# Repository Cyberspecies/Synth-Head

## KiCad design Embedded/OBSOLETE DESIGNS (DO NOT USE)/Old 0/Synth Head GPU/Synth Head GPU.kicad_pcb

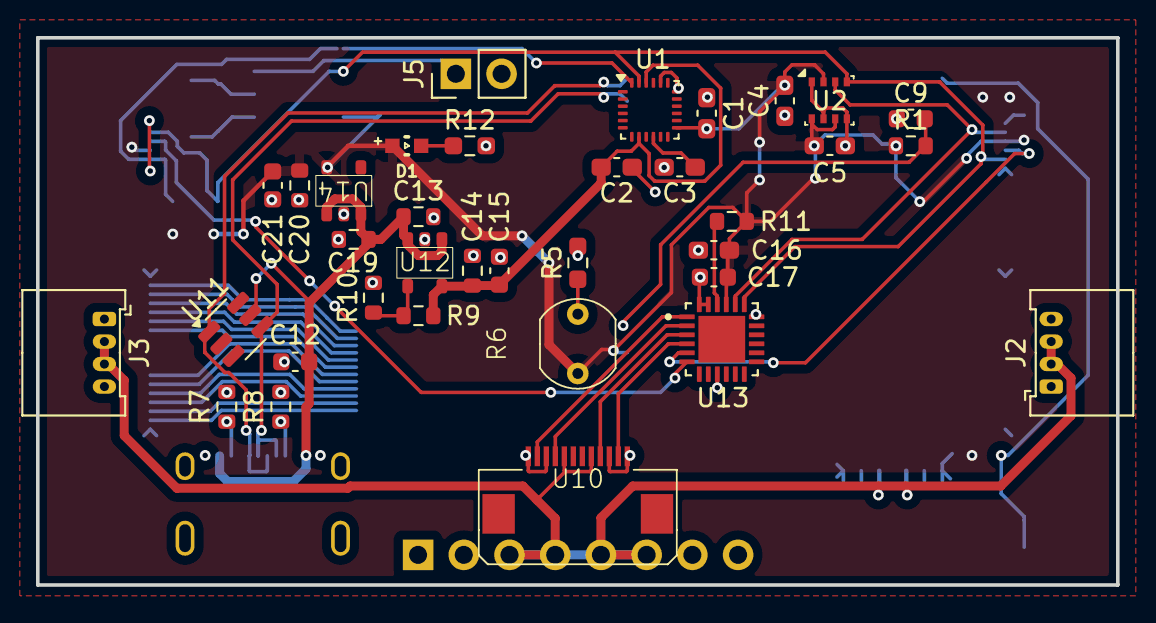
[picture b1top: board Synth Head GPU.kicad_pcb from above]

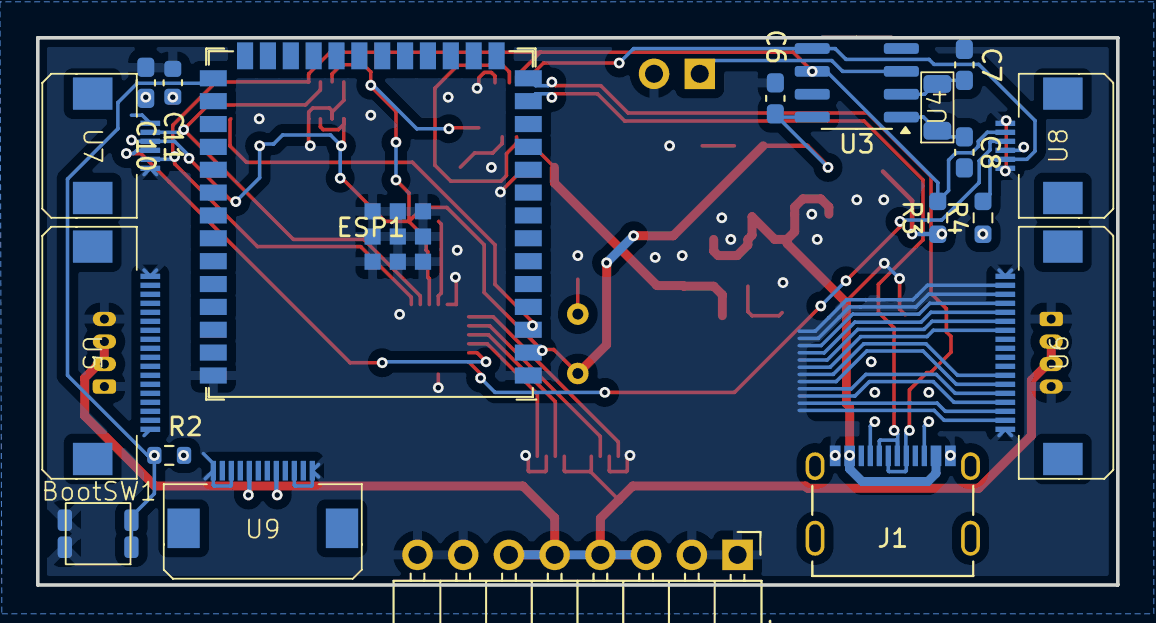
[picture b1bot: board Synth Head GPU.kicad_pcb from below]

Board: 2 copper layers, 60.0 x 30.4 mm, 54 parts (19 on the bottom side), 38 nets.

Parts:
BootSW1: SW_Push; Button-R-667843
C1, C2, C3, C6: 0.1uF; C_0603_1608Metric_Pad1.08x0.95mm_HandSolder
C4, C5: 100nF; C_0603_1608Metric_Pad1.08x0.95mm_HandSolder
C7, C8: 8pf; C_0603_1608Metric_Pad1.08x0.95mm_HandSolder
C9: 1uF; C_0603_1608Metric
C10, C16: 22uF; C_0603_1608Metric_Pad1.08x0.95mm_HandSolder
C11, C17: 0.1uF; C_0603_1608Metric
C12, C15, C21: 10uF; C_0603_1608Metric
C13, C14, C19, C20: 1uF; R_0603_1608Metric
D1: WL-SMCW_0603
ESP1: ESP32-S3-WROOM-1; ESP32-S3-WROOM-1U
J1: 10171746-00021LF; AMPHENOL_10171746-00021LF
J2, J3: JST [D]; Molex_PicoBlade_53048-0410_1x04_P1.25mm_Horizontal
J4: JST [G]; PinHeader_1x08_P2.54mm_Horizontal
J5: Coin Cell; PinHeader_1x02_P2.54mm_Vertical
R1, R2, R11: 10K; R_0603_1608Metric
R3, R4, R5: 10K; R_0603_1608Metric_Pad0.98x0.95mm_HandSolder
R6: R_Photo; Photoresistor Aliexpress
R7, R8: 5.1K; R_0603_1608Metric
R9: 75K; R_0603_1608Metric
R10: 60K; R_0603_1608Metric
R12: 65; R_0603_1608Metric_Pad0.98x0.95mm_HandSolder
U1: ICM-20948; InvenSense_QFN-24_3x3mm_P0.4mm
U2: BME280; Bosch_LGA-8_2.5x2.5mm_P0.65mm_ClockwisePinNumbering
U3: MCP7940N-xSN; SOIC-8_3.9x4.9mm_P1.27mm
U4: MP05346
U5, U6: FFC [D]; FFC Aliexpress 0.5mm 18P
U7, U8: FFC [C]; FFC Aliexpress 0.5mm 6P
U9: FFC [U]; FFC Aliexpress 0.5mm 12P
U10: FFC [G]; FFC Aliexpress 0.5mm 12P
U11: SRV05-4; SOT-23-6
U12: AP7366-W5-7; AP7366
U13: TCA9535RTWR; QFN50P400X400X80-25N
U14: AP7366-33W5-7; AP7366

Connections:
+1V8: C2.2, C14.1, C15.1, R9.1, U1.8 (VDDIO), U1.22 (~CS), U12.5 (Vout)
+3V3: C1.1, C4.2, C5.1, C6.2, C10.1, C11.1, C16.1, C17.1, C20.1, C21.1, D1.2, ESP1.2 (3V3), R1.1, R2.1, R3.1, R4.1, R6.1, R11.1, U1.13 (VDD), U2.2 (CSB), U2.6 (VDDIO), U2.8 (VDD), U3.8 (VCC), U7.3, U8.3, U13.21 (VCC), U14.5 (Vout)
+5V: C12.1, C13.1, C19.1, J1.A4_B9 (VBUS_A), J1.B4_A9 (VBUS_B), J2.2, J2.3, J3.2, J3.3, J4.3, J4.4, J4.5, J4.6, U5.8, U5.11, U6.8, U6.11, U9.5, U9.8, U10.5, U10.8, U11.5 (VP), U12.1 (VCC), U12.3 (EN), U14.1 (VCC), U14.3 (EN)
CPU IO 0: U10.2, U13.1 (P00)
CPU IO 1: U10.4, U13.2 (P01)
CPU IO 2: U10.9, U13.3 (P02)
CPU IO 3: U10.11, U13.4 (P03)
Disp 0: U5.17, U6.2
Disp 1: U5.16, U6.3
Disp 2: U5.15, U6.4
Disp 3: U5.14, U6.5
Disp 4: U5.13, U6.6
Disp 5: U5.12, U6.7
Disp 6: U5.7, U6.12
Disp 7: U5.6, U6.13
Disp 8: U5.5, U6.14
Disp 9: U5.4, U6.15
Disp 10: U5.3, U6.16
Disp 11: U5.2, U6.17
GND: BootSW1.2, C1.2, C2.1, C3.2, C4.1, C5.2, C6.1, C7.2, C8.2, C9.1, C10.2, C11.2, C12.2, C13.2, C14.2, C15.2, C16.2, C17.2, C19.2, C20.2, C21.2, ESP1.1 (GND), ESP1.40 (GND), ESP1.41 (GND), J1.A1_B12 (GND_A), J1.B1_A12 (GND_B), J2.1, J2.4, J3.1, J3.4, J4.1, J4.2, J4.7, J4.8, J5.2, R5.2, R7.2, R8.2, R10.2, R12.2, U1.9 (SDO/AD0), U1.18 (GND), U1.20 (GND), U2.1 (GND), U2.5 (SDO), U2.7 (GND), U3.4 (VSS), U5.1, U5.18, U6.1, U6.18, U7.1, U7.6, U8.1, U8.6, U9.1, U9.3, U9.10, U9.12, U10.1, U10.3, U10.10, U10.12, U11.2 (VN), U12.2 (GND), U13.9 (GND), U13.18 (A0), U13.23 (A1), U13.24 (A2), U13.25 (EP), U14.2 (GND)
unnamed: D1.1, R12.1
unnamed: C9.2, ESP1.3 (EN), R1.2
unnamed: BootSW1.1, ESP1.27 (GPIO0/BOOT), R2.2
unnamed: J1.A5 (CC1), R8.1
unnamed: J1.B5 (CC2), R7.1
unnamed: J5.1, U3.3 (VBAT)
unnamed: C3.1, U1.10 (REGOUT)
unnamed: C8.1, U3.1 (X1), U4.2
unnamed: C7.1, U3.2 (X2), U4.1
unnamed: R9.2, R10.1, U12.4 (ADJ)
unnamed: R11.2, U13.22 (~INT)
Photoresistor: R5.1, R6.2
SCL: R3.2, U1.23 (SCL/SCLK), U2.4 (SCK), U3.6 (SCL), U7.5, U8.5, U13.19 (SCL)
SDA: R4.2, U1.24 (SDA/SDI), U2.3 (SDI), U3.5 (SDA), U7.2, U8.2, U13.20 (SDA)
USB +: ESP1.14 (GPIO20/U1CTS/ADC2_CH9/CLK_OUT1/USB_D+), J1.A6 (DP1), J1.B6 (DP2), U11.1 (IO1)
USB -: ESP1.13 (GPIO19/U1RTS/ADC2_CH8/CLK_OUT2/USB_D-), J1.A7 (DN1), J1.B7 (DN2), U11.4 (IO3)
XShut 0: U7.4, U13.5 (P04)
XShut 1: U8.4, U13.6 (P05)

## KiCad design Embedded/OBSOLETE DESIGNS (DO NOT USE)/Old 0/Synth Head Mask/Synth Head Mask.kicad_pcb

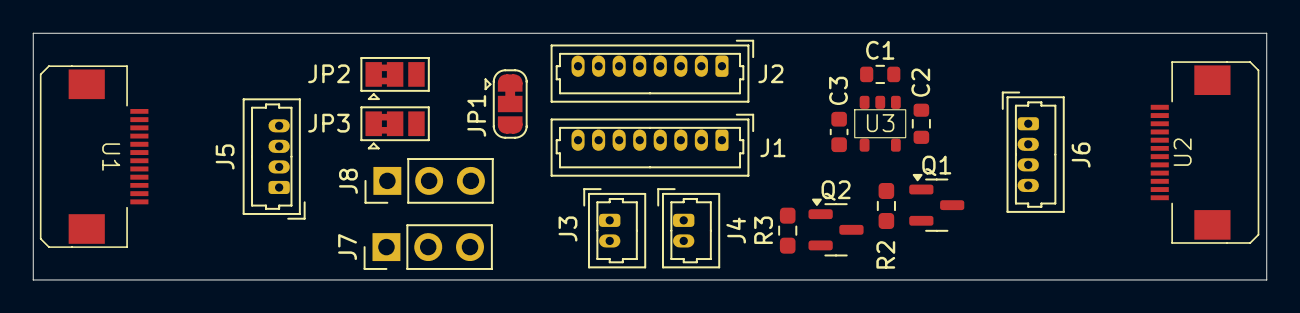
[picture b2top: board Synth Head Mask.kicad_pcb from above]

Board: 2 copper layers, 75.0 x 15.0 mm, 21 parts (0 on the bottom side), 18 nets, no tracks yet.

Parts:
C1, C2: 1uF; R_0603_1608Metric
C3: 10uF; C_0603_1608Metric
J1: JST [S]; Molex_PicoBlade_53047-0810_1x08_P1.25mm_Vertical
J2: JST [M]; Molex_PicoBlade_53047-0810_1x08_P1.25mm_Vertical
J3, J4: JST [F]; Molex_PicoBlade_53047-0210_1x02_P1.25mm_Vertical
J5: JST [B]; Molex_PicoBlade_53047-0410_1x04_P1.25mm_Vertical
J6: JST [K]; Molex_PicoBlade_53047-0410_1x04_P1.25mm_Vertical
J7, J8: Misc Expansion; PinHeader_1x03_P2.54mm_Vertical
JP1: LR Select; SolderJumper-3_P1.3mm_Bridged12_RoundedPad1.0x1.5mm
JP2, JP3: Expansion PWR; SolderJumper-3_P1.3mm_Bridged2Bar12_Pad1.0x1.5mm
Q1: BSS138; SOT-23
Q2: AS2302; SOT-23
R2, R3: 10K; R_0603_1608Metric_Pad0.98x0.95mm_HandSolder
U1: FFC [M]; FFC Aliexpress 0.5mm 12P
U2: FFC [S]; FFC Aliexpress 0.5mm 12P
U3: AP7366-33W5-7; AP7366

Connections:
+3V3: C2.1, C3.1, J1.3, J1.6, J2.3, J2.6, JP1.3 (B), JP2.1 (A), JP3.1 (A), Q1.1 (G), R2.1, U3.5 (Vout)
+5V: C1.1, J5.2, J5.3, J6.2, J6.3, JP2.3 (B), JP3.3 (B), Q2.3 (D), R3.1, U1.5, U1.8, U2.5, U2.8, U3.1 (VCC), U3.3 (EN)
CPU IO 0: J7.2, U1.4
CPU IO 1: J8.2, U1.9
Fan PWR: J3.1, J4.1, Q2.2 (S)
GND: C1.2, C2.2, C3.2, J1.1, J1.2, J1.7, J1.8, J2.1, J2.8, J3.2, J4.2, J5.1, J5.4, J6.1, J6.4, J7.3, J8.3, JP1.1 (A), U1.1, U1.2, U1.3, U1.10, U1.11, U1.12, U2.1, U2.12, U3.2 (GND)
unnamed: J2.7, JP1.2 (C)
unnamed: J7.1, JP2.2 (C)
unnamed: J8.1, JP3.2 (C)
unnamed: Q1.3 (D), Q2.1 (G), R3.2
Snoot IO 0: Q1.2 (S), R2.2, U2.4
Snoot RX: U1.6, U2.6
Snoot SCK: J2.4, U2.11
Snoot SCL: J1.4, U2.3
Snoot SD: J2.2, U2.9
Snoot SDA: J1.5, U2.2
Snoot TX: U1.7, U2.7
Snoot WS: J2.5, U2.10

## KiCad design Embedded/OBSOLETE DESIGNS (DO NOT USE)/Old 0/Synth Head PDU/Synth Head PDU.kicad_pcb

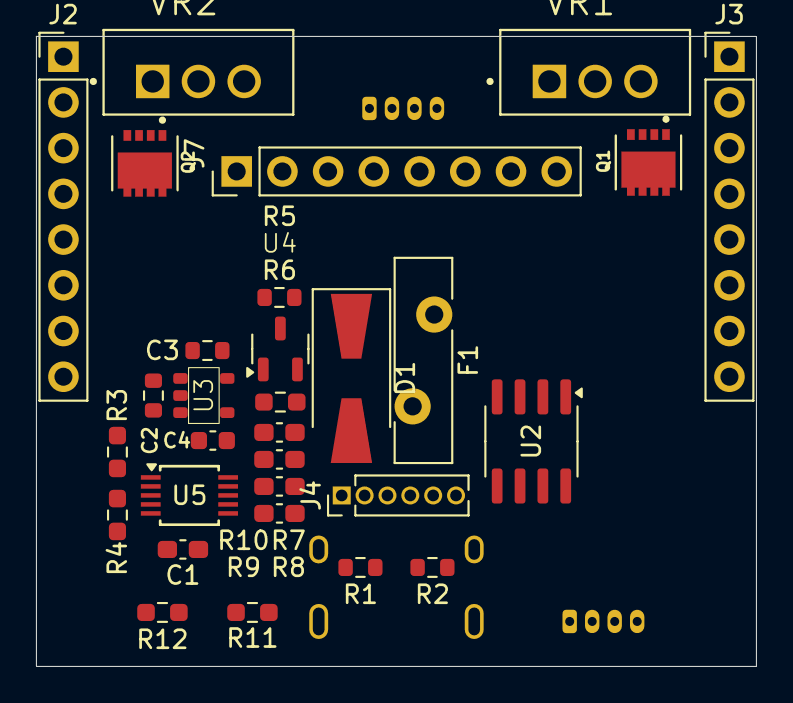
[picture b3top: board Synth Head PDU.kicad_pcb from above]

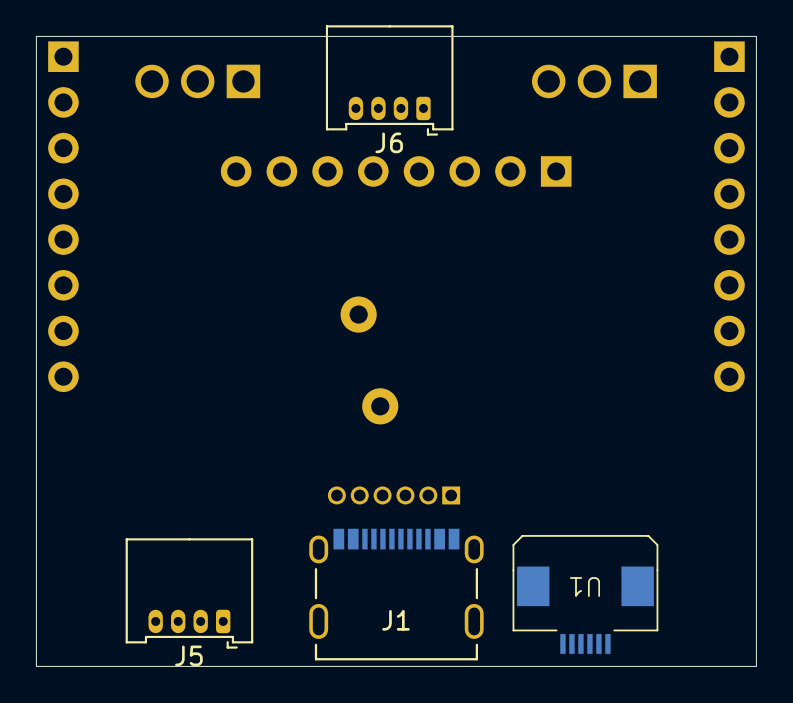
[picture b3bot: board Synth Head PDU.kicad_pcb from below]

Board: 2 copper layers, 40.0 x 35.0 mm, 34 parts (4 on the bottom side), 22 nets, no tracks yet.

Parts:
C1: 0.1uF; C_0603_1608Metric_Pad1.08x0.95mm_HandSolder
C2, C3: 1uF; R_0603_1608Metric
C4: 10uF; C_0603_1608Metric
D1: SL54A; D_SMA-SMB_Universal_Handsoldering
F1: BK16-500-SZ; Fuse_Bourns_MF-RHT500
J1: 10171746-00021LF; AMPHENOL_10171746-00021LF
J2, J3: JST [P]; PinHeader_1x08_P2.54mm_Vertical
J4: JST [USB]; PinHeader_1x06_P1.27mm_Vertical
J5: JST [C]; Molex_PicoBlade_53048-0410_1x04_P1.25mm_Horizontal
J6: JST [B]; Molex_PicoBlade_53048-0410_1x04_P1.25mm_Horizontal
J7: JST [G]; PinHeader_1x08_P2.54mm_Vertical
Q1, Q2: RQ3E100BNTB; TRANS_RQ3E100BNTB
R1, R2: 5.1K; R_0603_1608Metric
R3, R4: 4K; R_0603_1608Metric_Pad0.98x0.95mm_HandSolder
R5: 10K; R_0603_1608Metric
R6: 1K; R_0603_1608Metric_Pad0.98x0.95mm_HandSolder
R7, R9: 12K; C_0603_1608Metric_Pad1.08x0.95mm_HandSolder
R8, R10: 3K; C_0603_1608Metric_Pad1.08x0.95mm_HandSolder
R11, R12: 10K; R_0603_1608Metric_Pad0.98x0.95mm_HandSolder
U1: FFC [K]; FFC Aliexpress 0.5mm 6P
U2: TMCS1108A2BQDR; SOIC-8_3.9x4.9mm_P1.27mm
U3: AP7366-33W5-7; AP7366
U4: RSC002P03
U5: ADS1015IDGS; TSSOP-10_3x3mm_P0.5mm
VR1, VR2: LM1084IT-5.0_NOPB; TO254P1054X470X1955-3

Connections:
+3V3: C1.1, C3.1, C4.1, R11.1, R12.1, U2.8 (VS), U3.5 (Vout), U5.8 (VDD)
+5V: J5.2, J5.3, J6.2, J6.3, J7.3, J7.4, J7.5, J7.6, U2.3 (Output), U2.4 (Output)
Analog Current: U2.7 (Vout), U5.5 (AIN1)
Analog Voltage: R3.2, R4.1, U5.4 (AIN0)
Fin Batt Voltage 0: R7.2, R8.1, U5.6 (AIN2)
Fin Batt Voltage 1: R9.2, R10.1, U5.7 (AIN3)
GND: C1.2, C2.2, C3.2, C4.2, J1.A1_B12 (GND_A), J1.B1_A12 (GND_B), J1.SH1 (SHIELD), J1.SH2 (SHIELD__1), J1.SH3 (SHIELD__2), J1.SH4 (SHIELD__3), J2.1, J2.2, J2.7, J2.8, J3.1, J3.2, J3.7, J3.8, J4.1, J4.6, J5.1, J5.4, J6.1, J6.4, J7.1, J7.2, J7.7, J7.8, R1.2, R2.2, R4.2, R5.2, R8.2, R10.2, U1.1, U1.6, U2.5 (GND), U3.2 (GND), U5.1 (ADDR), U5.3 (GND), VR1.1 (ADJ/GND), VR2.1 (ADJ/GND)
unnamed: D1.1 (K), F1.1
unnamed: J1.A5 (CC1), R2.1
unnamed: J1.B5 (CC2), R1.1
unnamed: Q1.4, Q2.4, R5.1, U4.3 (D)
unnamed: R6.2, U4.1 (G)
unnamed: Q1.1_3, VR1.3 (INPUT)
unnamed: Q2.1_3, VR2.3 (INPUT)
PWR: C2.1, F1.2, R3.1, U2.1 (Input), U2.2 (Input), U3.1 (VCC), U3.3 (EN), VR1.2 (OUTPUT), VR2.2 (OUTPUT)
Raw PWR 0: J2.3, J2.4, J2.5, J2.6, Q1.5_8, R7.1
Raw PWR 1: J3.3, J3.4, J3.5, J3.6, Q2.5_8, R9.1
SCL: R11.2, U1.5, U5.9 (SDA)
SDA: R12.2, U1.2, U5.10 (SCL)
USB +: J1.A6 (DP1), J1.B6 (DP2), J4.3, U1.3
USB -: J1.A7 (DN1), J1.B7 (DN2), J4.4, U1.4
USB PWR: D1.2 (A), J1.A4_B9 (VBUS_A), J1.B4_A9 (VBUS_B), J4.2, J4.5, R6.1, U4.2 (S)

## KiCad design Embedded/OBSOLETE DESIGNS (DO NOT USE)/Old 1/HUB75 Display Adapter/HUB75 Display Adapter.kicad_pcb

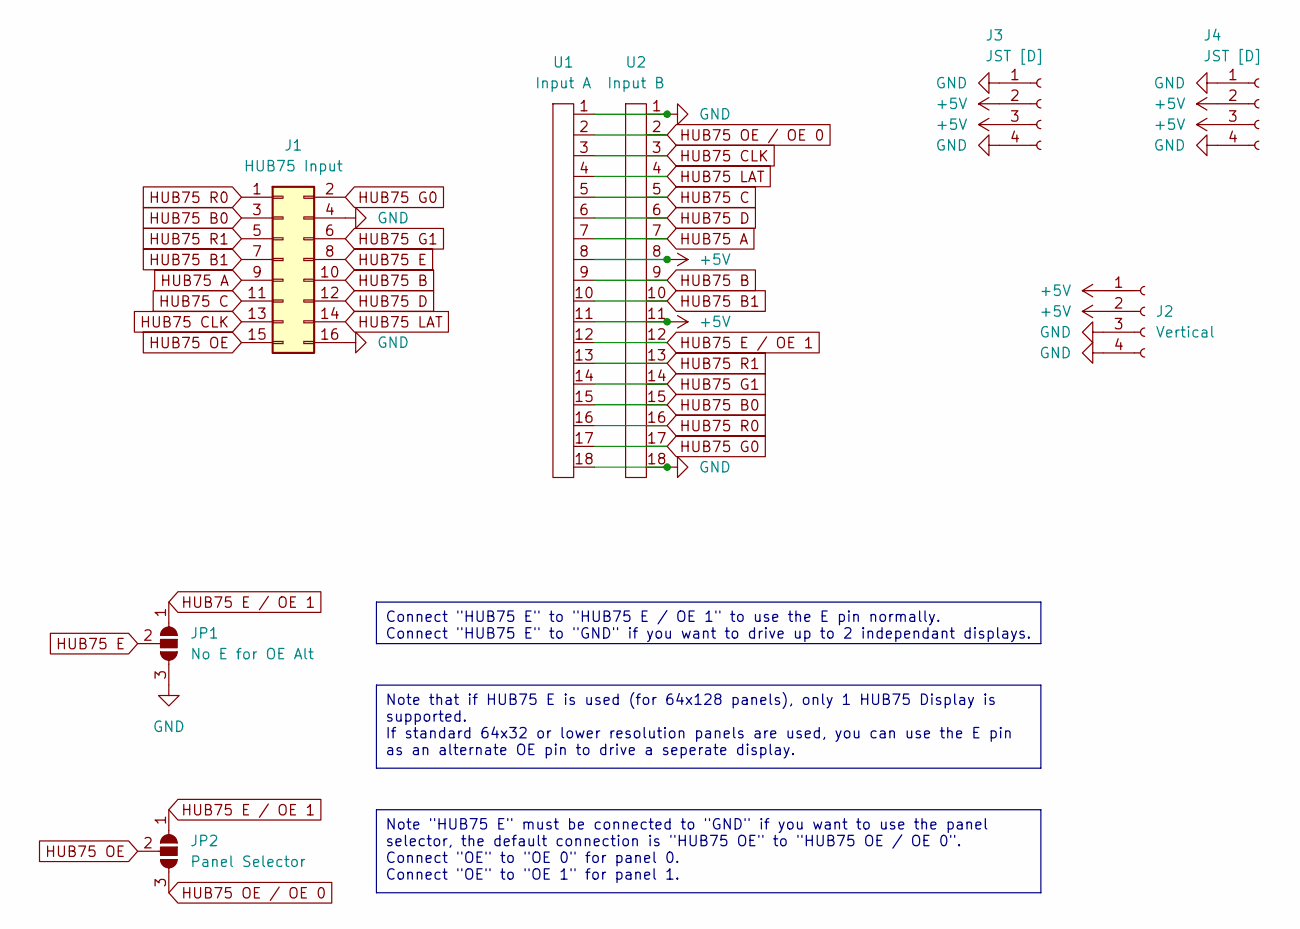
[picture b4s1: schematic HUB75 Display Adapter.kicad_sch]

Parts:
J1: HUB75 Input; PinHeader_2x08_P2.54mm_Vertical
J2: Vertical; Molex_KK-396_5273-04A_1x04_P3.96mm_Vertical
J3, J4: JST [D]; Molex_PicoBlade_53048-0410_1x04_P1.25mm_Horizontal
JP1: No E for OE Alt; SolderJumper-3_P1.3mm_Open_RoundedPad1.0x1.5mm_NumberLabels
JP2: Panel Selector; SolderJumper-3_P1.3mm_Open_RoundedPad1.0x1.5mm_NumberLabels
U1: Input A; FFC Aliexpress 0.5mm 18P
U2: Input B; FFC Aliexpress 0.5mm 18P

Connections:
+5V: J2.1, J2.2, J3.2, J3.3, J4.2, J4.3, U1.8, U1.11, U2.8, U2.11
GND: J1.4, J1.16, J2.3, J2.4, J3.1, J3.4, J4.1, J4.4, JP1.3 (B), U1.1, U1.18, U2.1, U2.18
HUB75 A: J1.9, U1.7, U2.7
HUB75 B: J1.10, U1.9, U2.9
HUB75 B0: J1.3, U1.15, U2.15
HUB75 B1: J1.7, U1.10, U2.10
HUB75 C: J1.11, U1.5, U2.5
HUB75 CLK: J1.13, U1.3, U2.3
HUB75 D: J1.12, U1.6, U2.6
HUB75 E: J1.8, JP1.2 (C)
HUB75 E / OE 1: JP1.1 (A), JP2.1 (A), U1.12, U2.12
HUB75 G0: J1.2, U1.17, U2.17
HUB75 G1: J1.6, U1.14, U2.14
HUB75 LAT: J1.14, U1.4, U2.4
HUB75 OE: J1.15, JP2.2 (C)
HUB75 OE / OE 0: JP2.3 (B), U1.2, U2.2
HUB75 R0: J1.1, U1.16, U2.16
HUB75 R1: J1.5, U1.13, U2.13

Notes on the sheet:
Note that if HUB75 E is used (for 64x128 panels), only 1 HUB75 Display is supported. If standard 64x32 or lower resolution panels are used, you can use the E pin as an alternate OE pin to drive a seperate display.
Connect "HUB75 E" to "HUB75 E / OE 1" to use the E pin normally. Connect "HUB75 E" to "GND" if you want to drive up to 2 independant displays.
Note "HUB75 E" must be connected to "GND" if you want to use the panel selector, the default connection is "HUB75 OE" to "HUB75 OE / OE 0". Connect "OE" to "OE 0" for panel 0. Connect "OE" to "OE 1" for panel 1.

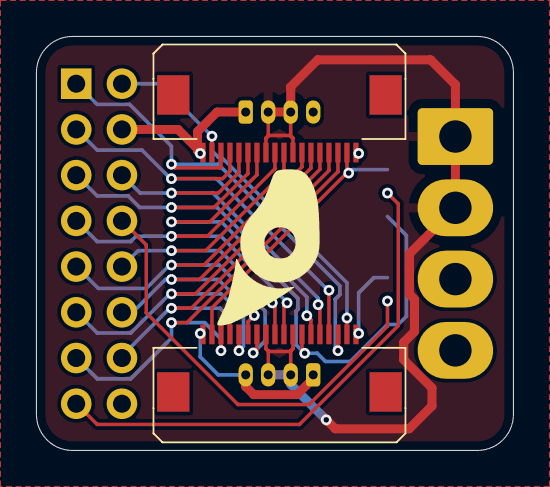
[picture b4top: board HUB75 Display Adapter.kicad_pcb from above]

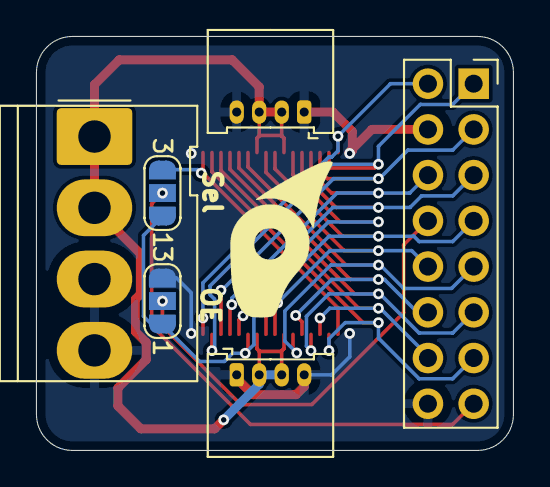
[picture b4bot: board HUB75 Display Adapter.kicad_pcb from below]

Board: 2 copper layers, 26.5 x 23.0 mm, 8 parts (6 on the bottom side), 18 nets.

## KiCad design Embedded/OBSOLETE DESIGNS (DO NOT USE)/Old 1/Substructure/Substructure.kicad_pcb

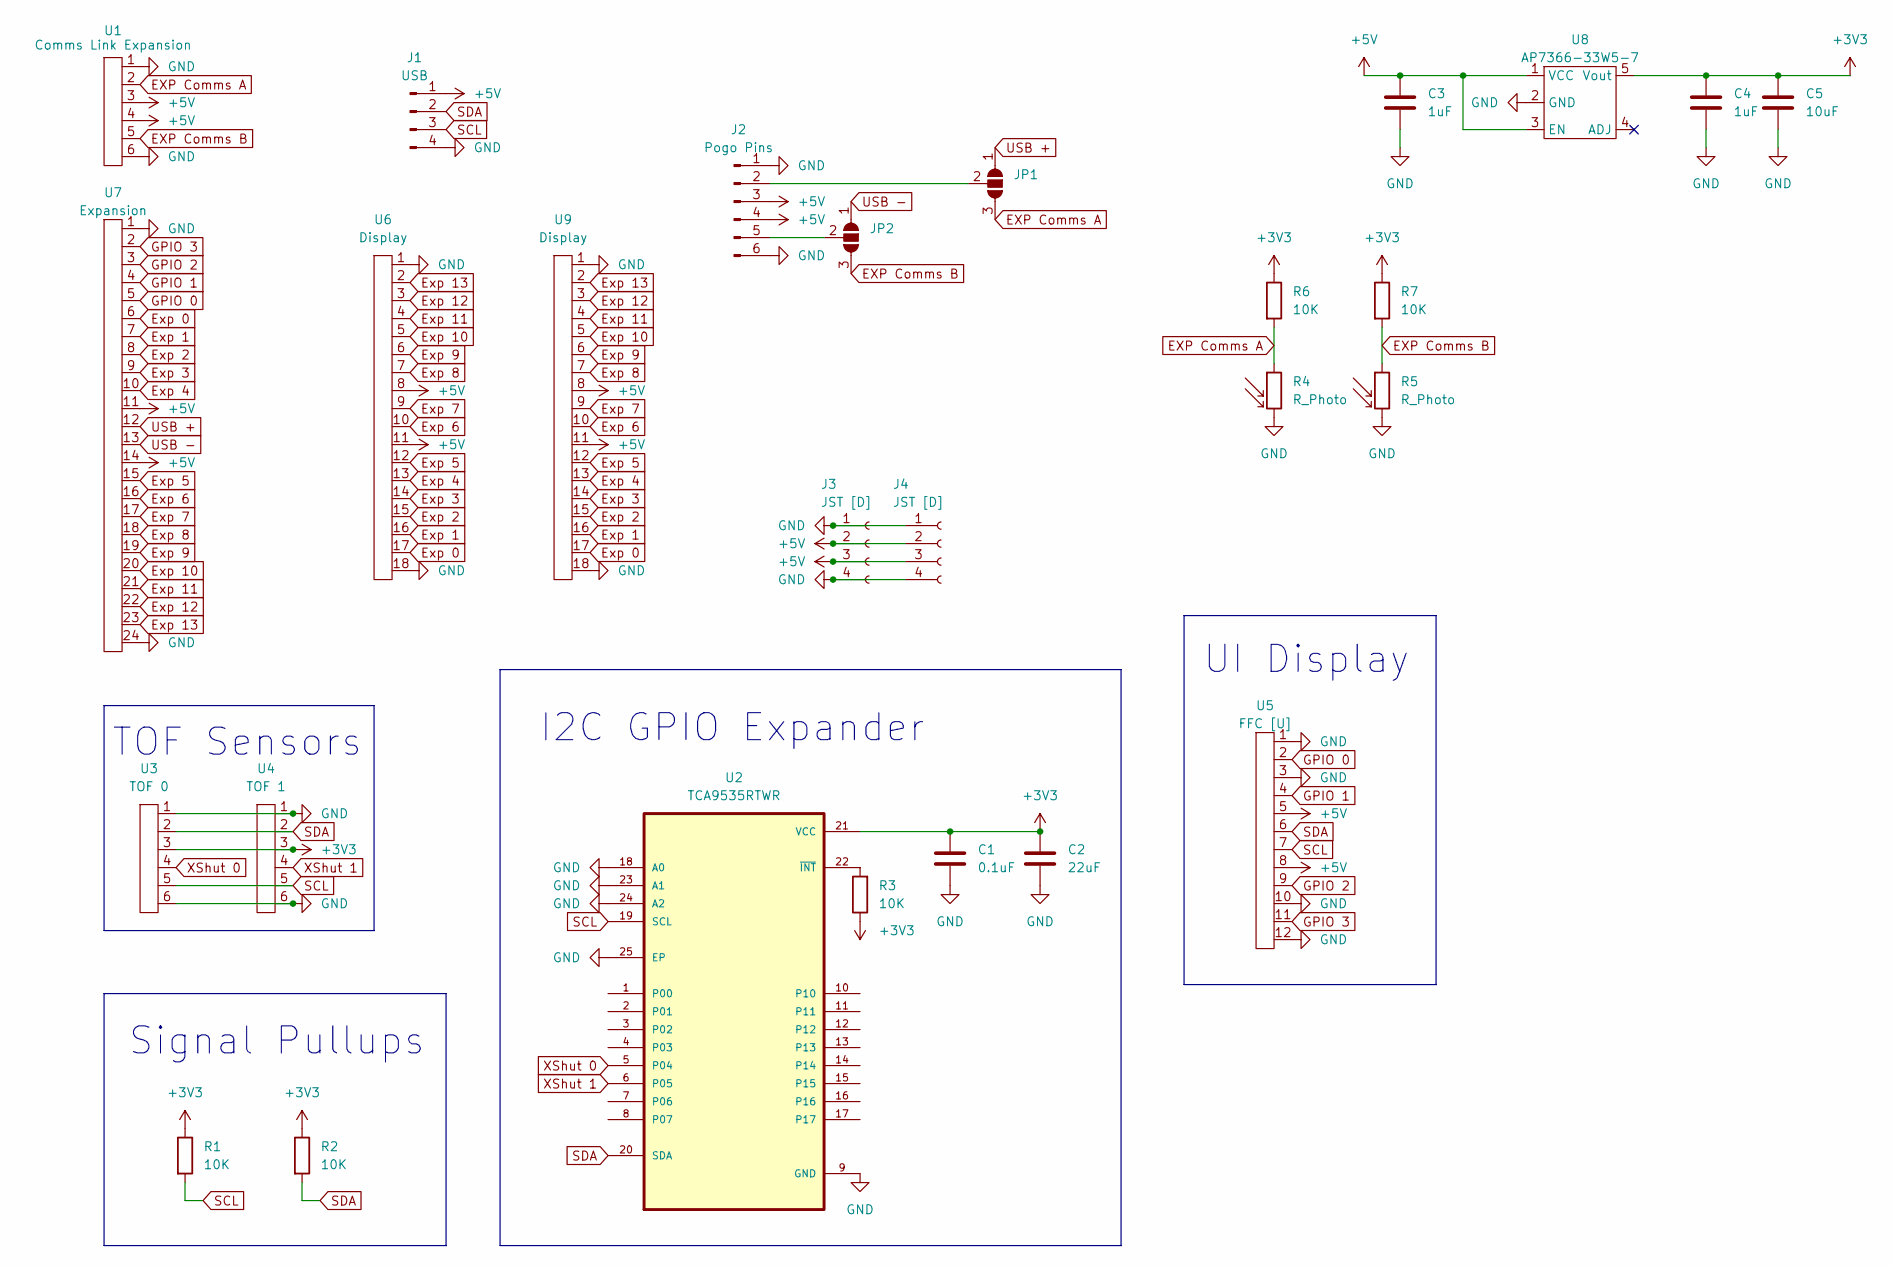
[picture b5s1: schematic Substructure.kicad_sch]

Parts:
C1: 0.1uF; C_0603_1608Metric
C2: 22uF; C_0603_1608Metric_Pad1.08x0.95mm_HandSolder
C3, C4: 1uF; R_0603_1608Metric
C5: 10uF; C_0603_1608Metric
J1: USB; Hirose_DF13-04P-1.25DS_1x04_P1.25mm_Horizontal
J2: Pogo Pins; PinHeader_1x06_P2.54mm_Vertical
J3, J4: JST [D]; Molex_PicoBlade_53048-0410_1x04_P1.25mm_Horizontal
JP1, JP2: SolderJumper_3_Open; SolderJumper-3_P1.3mm_Open_RoundedPad1.0x1.5mm
R1, R2, R6, R7: 10K; R_0603_1608Metric_Pad0.98x0.95mm_HandSolder
R3: 10K; R_0603_1608Metric
R4, R5: R_Photo; Photoresistor Aliexpress
U1: Comms Link Expansion; FFC Aliexpress 0.5mm 6P
U2: TCA9535RTWR; QFN50P400X400X80-25N
U3: TOF 0; Hirose_DF13-06P-1.25DS_1x06_P1.25mm_Horizontal
U4: TOF 1; Hirose_DF13-06P-1.25DS_1x06_P1.25mm_Horizontal
U5: FFC [U]; FFC Aliexpress 0.5mm 12P
U6, U9: Display; FFC Aliexpress 0.5mm 18P
U7: Expansion; FFC Aliexpress 0.5mm 24P
U8: AP7366-33W5-7; AP7366

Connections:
+3V3: C1.1, C2.1, C4.1, C5.1, R1.1, R2.1, R3.1, R6.1, R7.1, U2.21 (VCC), U3.3, U4.3, U8.5 (Vout)
+5V: C3.1, J1.1, J2.3, J2.4, J3.2, J3.3, J4.2, J4.3, U1.3, U1.4, U5.5, U5.8, U6.8, U6.11, U7.11, U7.14, U8.1 (VCC), U8.3 (EN), U9.8, U9.11
EXP Comms A: JP1.3 (B), R4.1, R6.2, U1.2
EXP Comms B: JP2.3 (B), R5.1, R7.2, U1.5
Exp 0: U6.17, U7.6, U9.17
Exp 1: U6.16, U7.7, U9.16
Exp 2: U6.15, U7.8, U9.15
Exp 3: U6.14, U7.9, U9.14
Exp 4: U6.13, U7.10, U9.13
Exp 5: U6.12, U7.15, U9.12
Exp 6: U6.10, U7.16, U9.10
Exp 7: U6.9, U7.17, U9.9
Exp 8: U6.7, U7.18, U9.7
Exp 9: U6.6, U7.19, U9.6
Exp 10: U6.5, U7.20, U9.5
Exp 11: U6.4, U7.21, U9.4
Exp 12: U6.3, U7.22, U9.3
Exp 13: U6.2, U7.23, U9.2
GND: C1.2, C2.2, C3.2, C4.2, C5.2, J1.4, J2.1, J2.6, J3.1, J3.4, J4.1, J4.4, R4.2, R5.2, U1.1, U1.6, U2.9 (GND), U2.18 (A0), U2.23 (A1), U2.24 (A2), U2.25 (EP), U3.1, U3.6, U4.1, U4.6, U5.1, U5.3, U5.10, U5.12, U6.1, U6.18, U7.1, U7.24, U8.2 (GND), U9.1, U9.18
GPIO 0: U5.2, U7.5
GPIO 1: U5.4, U7.4
GPIO 2: U5.9, U7.3
GPIO 3: U5.11, U7.2
unnamed: J2.2, JP1.2 (C)
unnamed: J2.5, JP2.2 (C)
unnamed: R3.2, U2.22 (~INT)
SCL: J1.3, R1.2, U2.19 (SCL), U3.5, U4.5, U5.7
SDA: J1.2, R2.2, U2.20 (SDA), U3.2, U4.2, U5.6
USB +: JP1.1 (A), U7.12
USB -: JP2.1 (A), U7.13
XShut 0: U2.5 (P04), U3.4
XShut 1: U2.6 (P05), U4.4

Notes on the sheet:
Signal Pullups
UI Display
I2C GPIO Expander
TOF Sensors

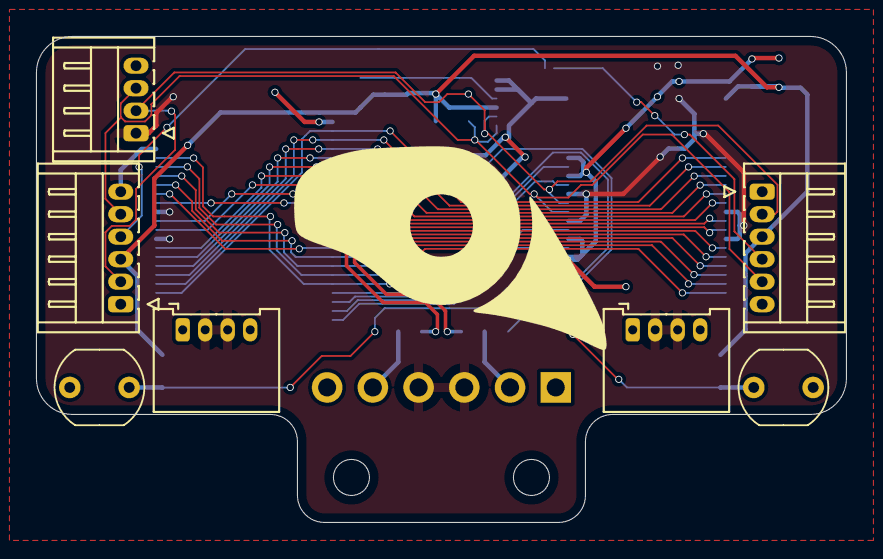
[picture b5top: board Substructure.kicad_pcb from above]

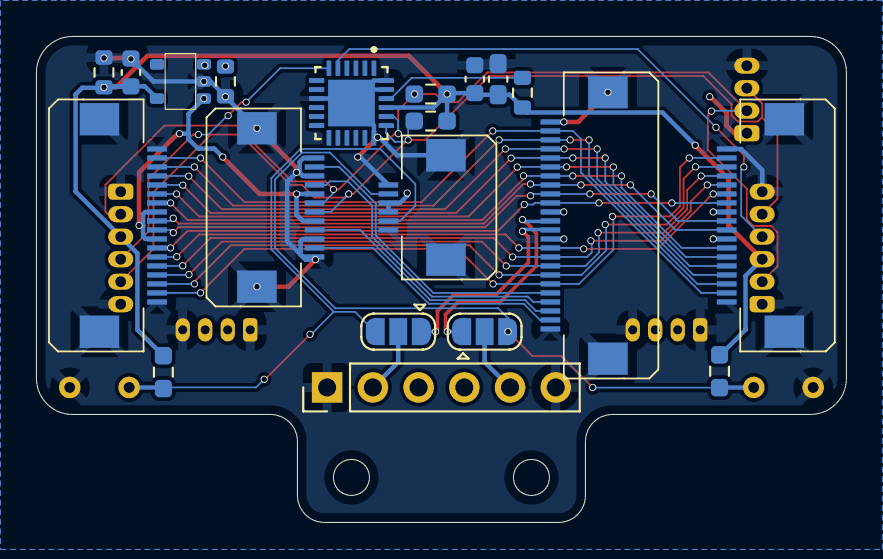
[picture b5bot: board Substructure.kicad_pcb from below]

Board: 2 copper layers, 45.0 x 27.0 mm, 27 parts (20 on the bottom side), 32 nets.

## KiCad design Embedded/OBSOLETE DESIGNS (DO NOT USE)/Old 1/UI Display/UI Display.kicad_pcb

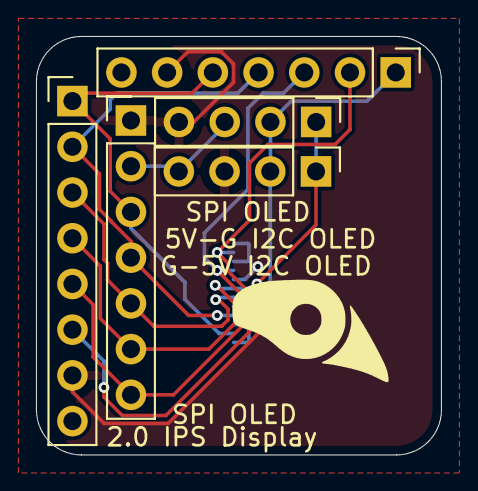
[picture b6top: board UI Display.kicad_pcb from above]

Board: 2 copper layers, 22.5 x 23.2 mm, 6 parts (1 on the bottom side), 8 nets.

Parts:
J1: 2.0 IPS Display; PinHeader_1x08_P2.54mm_Vertical
J2, J5: SPI OLED; PinHeader_1x07_P2.54mm_Vertical
J3: 5V-G I2C OLED; PinHeader_1x04_P2.54mm_Vertical
J4: G-5V I2C OLED; PinHeader_1x04_P2.54mm_Vertical
U2: FFC [U]; FFC Aliexpress 0.5mm 12P

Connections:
+5V: J1.7, J2.1, J3.4, J4.3, J5.6, U2.5, U2.8
GND: J1.8, J2.2, J3.3, J4.4, J5.7, U2.1, U2.3, U2.10, U2.12
UI 0: J1.1, J2.3, J5.5, U2.2
UI 1: J1.2, J2.4, J5.4, U2.4
UI 2: J1.5, J2.7, J5.3, U2.9
UI 3: J1.6, J5.2, U2.11
UI IO 0: J1.3, J2.5, J3.2, J4.2, J5.1, U2.6
UI IO 1: J1.4, J2.6, J3.1, J4.1, U2.7

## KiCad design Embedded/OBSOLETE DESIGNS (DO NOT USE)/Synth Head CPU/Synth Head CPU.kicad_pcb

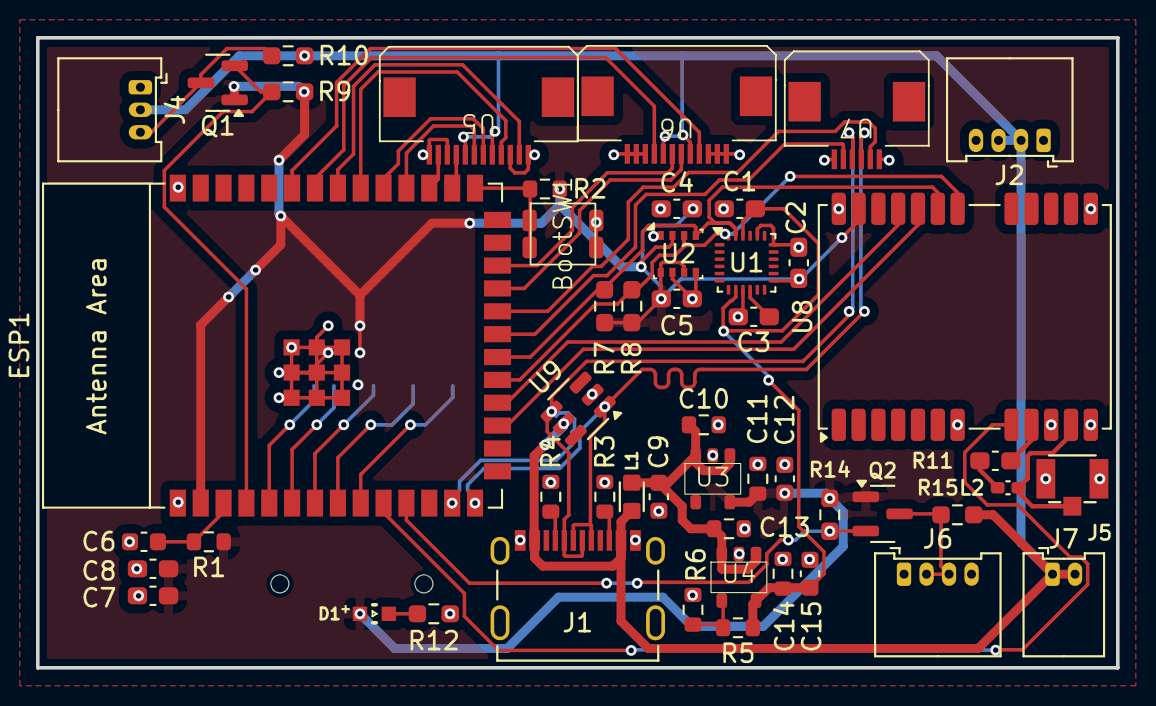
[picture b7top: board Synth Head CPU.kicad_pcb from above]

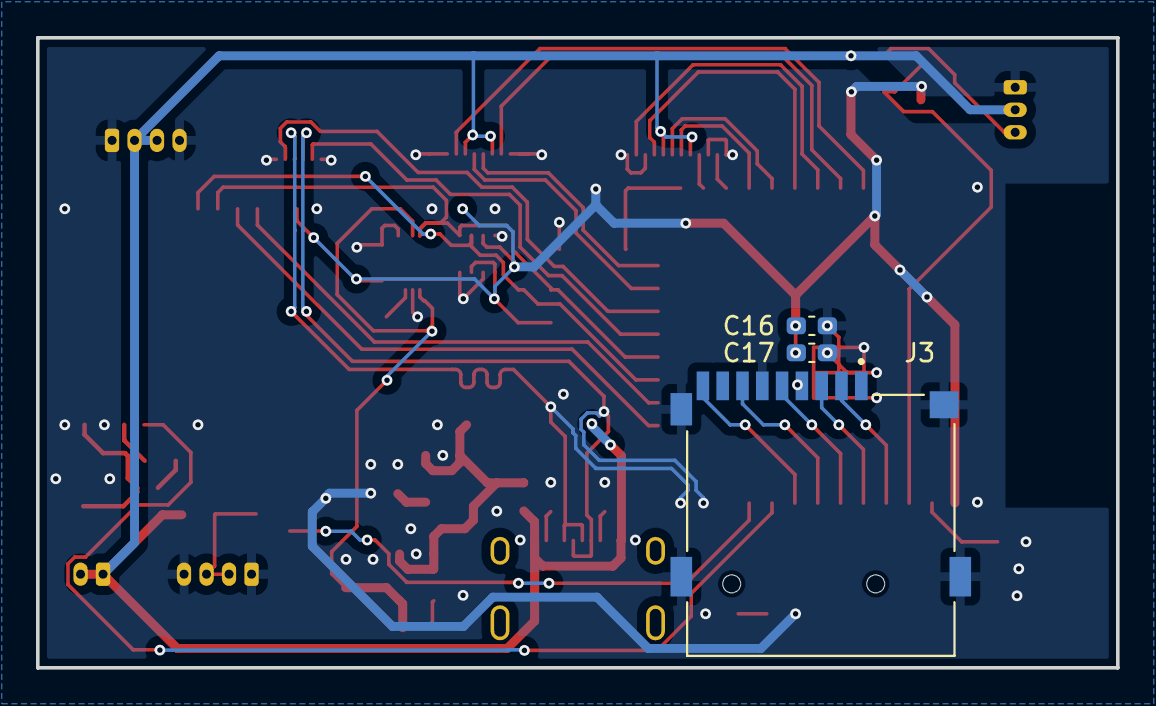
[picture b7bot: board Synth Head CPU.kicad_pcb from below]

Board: 2 copper layers, 60.0 x 35.0 mm, 54 parts (3 on the bottom side), 43 nets.

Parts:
BootSW1: SW_Push; Button-R-667843
C1, C2, C3, C8, C17: 0.1uF; C_0603_1608Metric_Pad1.08x0.95mm_HandSolder
C4, C5: 100nF; C_0603_1608Metric_Pad1.08x0.95mm_HandSolder
C6: 1uF; C_0603_1608Metric
C7, C16: 22uF; C_0603_1608Metric_Pad1.08x0.95mm_HandSolder
C9, C12, C15: 10uF; C_0603_1608Metric
C10, C11, C13, C14: 1uF; R_0603_1608Metric
D1: WL-SMCW_0603
ESP1: ESP32-S3-WROOM-1
J1: 10171746-00021LF; AMPHENOL_10171746-00021LF
J2: JST [C]; Molex_PicoBlade_53048-0410_1x04_P1.25mm_Horizontal
J3: MSD-1-A; CUI_MSD-1-A
J4: JST [N]; Molex_PicoBlade_53048-0310_1x03_P1.25mm_Horizontal
J5: U.FL-R-SMT-1_10_; HRS_U.FL-R-SMT-1_10_
J6: Pogo JST; Molex_PicoBlade_53048-0410_1x04_P1.25mm_Horizontal
J7: Pogo JST; Molex_PicoBlade_53048-0210_1x02_P1.25mm_Horizontal
L1: MPZ1608S601ATA00; INDC1608X95N
L2: LQG15HS27NJ02; L_0402_1005Metric_Pad0.77x0.64mm_HandSolder
Q1, Q2: BSS138; SOT-23
R1, R2: 10K; R_0603_1608Metric
R3, R4: 5.1K; R_0603_1608Metric
R5: 75K; R_0603_1608Metric
R6: 60K; R_0603_1608Metric
R7, R8, R9, R10, R14, R15: 10K; R_0603_1608Metric_Pad0.98x0.95mm_HandSolder
R11: 10; C_0603_1608Metric_Pad1.08x0.95mm_HandSolder
R12: 65; R_0603_1608Metric_Pad0.98x0.95mm_HandSolder
U1: ICM-20948; InvenSense_QFN-24_3x3mm_P0.4mm
U2: BME280; Bosch_LGA-8_2.5x2.5mm_P0.65mm_ClockwisePinNumbering
U3: AP7366-33W5-7; AP7366
U4: AP7366-W5-7; AP7366
U5: FFC [G]; FFC Aliexpress 0.5mm 12P
U6: FFC [M]; FFC Aliexpress 0.5mm 12P
U7: FFC [K]; FFC Aliexpress 0.5mm 6P
U8: NEO-M8M; ublox_NEO
U9: SRV05-4; SOT-23-6

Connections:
3V3 Jaw LEDS: ESP1.11 (GPIO18/U1RXD/ADC2_CH7/CLK_OUT3), Q2.2 (S), R14.2
3V3 Neck LEDS: ESP1.4 (GPIO4/TOUCH4/ADC1_CH3), Q1.2 (S), R9.2
+1V8: C1.2, C14.1, C15.1, R5.1, U1.8 (VDDIO), U1.22 (~CS), U4.5 (Vout)
+3V3: C2.1, C4.2, C5.1, C7.1, C8.1, C11.1, C12.1, C16.1, C17.1, D1.2, ESP1.2 (3V3), J3.4 (VDD), Q1.1 (G), Q2.1 (G), R1.1, R2.1, R7.1, R8.1, R9.1, R14.1, U1.13 (VDD), U2.2 (CSB), U2.6 (VDDIO), U2.8 (VDD), U3.5 (Vout), U8.23 (VCC)
+5V: J1.A4_B9 (VBUS_A), J1.B4_A9 (VBUS_B), J2.2, J2.3, J4.2, J7.1, J7.2, L1.1, R10.1, R15.1, U5.5, U5.8, U6.5, U6.8, U9.5 (VP)
/1V8 Regulator/Vin: C9.1, C10.1, C13.1, L1.2, U3.1 (VCC), U3.3 (EN), U4.1 (VCC), U4.3 (EN)
CPU-GPU GPIO 0: ESP1.33 (MTDO/GPIO40/CLK_OUT2), U5.2
CPU-GPU GPIO 1: ESP1.32 (MTCK/GPIO39/CLK_OUT3/SUBSPICS1), U5.4
CPU-GPU GPIO 2: ESP1.28 (SPIIO6/GPIO35/FSPID/SUBSPID), U5.9
CPU-GPU GPIO 3: ESP1.29 (SPIIO7/GPIO36/FSPICLK/SUBSPICLK), U5.11
CPU-GPU RX: ESP1.31 (GPIO38/FSPIWP/SUBSPIWP), U5.6
CPU-GPU TX: ESP1.30 (SPIDQS/GPIO37/FSPIQ/SUBSPIQ), U5.7
CPU-Mask GPIO 0: ESP1.35 (MTMS/GPIO42), U6.4
CPU-Mask GPIO 1: ESP1.34 (MTDI/GPIO41/CLK_OUT1), U6.9
CPU-Mask RX: ESP1.23 (GPIO21), U6.6
CPU-Mask TX: ESP1.24 (GPIO47/SPICLK_P/SUBSPICLK_P_DIFF), U6.7
CPU-PDU SCL: ESP1.21 (GPIO13/TOUCH13/ADC2_CH2/FSPIQ/FSPIIO7/S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), U7.5
CPU-PDU SDA: ESP1.22 (GPIO14/TOUCH14/ADC2_CH3/FSPIWP/FSPIDQS/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), U7.2
GND: BootSW1.2, C1.1, C2.2, C3.2, C4.1, C5.2, C6.1, C7.2, C8.2, C9.2, C10.2, C11.2, C12.2, C13.2, C14.2, C15.2, C16.2, C17.2, ESP1.1 (GND), ESP1.40 (GND), ESP1.41 (GND), J1.A1_B12 (GND_A), J1.B1_A12 (GND_B), J2.1, J2.4, J3.6 (VSS), J3.G1 (COVER_GND), J3.G2 (COVER_GND__1), J3.G3 (COVER_GND__2), J3.G4 (COVER_GND__3), J4.1, J5.1, J6.1, J6.4, R3.2, R4.2, R6.2, R12.2, U1.9 (SDO/AD0), U1.18 (GND), U1.20 (GND), U2.1 (GND), U2.5 (SDO), U2.7 (GND), U3.2 (GND), U4.2 (GND), U5.1, U5.3, U5.10, U5.12, U6.1, U6.2, U6.3, U6.10, U6.11, U6.12, U7.1, U7.6, U8.7 (VDD_USB), U8.10 (GND), U8.12 (GND), U8.13 (GND), U8.24 (GND), U9.2 (VN)
GPS Reset: ESP1.10 (GPIO17/U1TXD/ADC2_CH6), U8.8 (~RESET)
GPS UART RX: ESP1.18 (GPIO10/TOUCH10/ADC1_CH9/FSPICS0/FSPIIO4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), U8.21 (RXD/SPI_MOSI)
GPS UART TX: ESP1.17 (GPIO9/TOUCH9/ADC1_CH8/FSPIHD/SUBSPIHD), U8.20 (TXD/SPI_MISO)
Jaw LEDS: J6.2, J6.3, Q2.3 (D), R15.2
Neck LEDS: J4.3, Q1.3 (D), R10.2
unnamed: D1.1, R12.1
unnamed: C6.2, ESP1.3 (EN), R1.2
unnamed: BootSW1.1, ESP1.27 (GPIO0/BOOT), R2.2
unnamed: J1.A5 (CC1), R4.1
unnamed: J1.B5 (CC2), R3.1
unnamed: L2.1, R11.2
unnamed: C3.1, U1.10 (REGOUT)
unnamed: R5.2, R6.1, U4.4 (ADJ)
unnamed: J5.2, L2.2, U8.11 (RF_IN)
unnamed: R11.1, U8.9 (VCC_RF)
SCL: ESP1.20 (GPIO12/TOUCH12/ADC2_CH1/FSPICLK/FSPIIO6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), R7.2, U1.23 (SCL/SCLK), U2.4 (SCK), U8.19 (SCL/SPI_CLK)
SD Card CLK: ESP1.7 (GPIO7/TOUCH7/ADC1_CH6), J3.5 (CLK)
SD Card CS: ESP1.5 (GPIO5/TOUCH5/ADC1_CH4), J3.2 (CD/DAT3)
SD Card Detect: ESP1.9 (GPIO16/U0CTS/ADC2_CH5/XTAL_32K_N), J3.CD
SD Card MISO: ESP1.8 (GPIO15/U0RTS/ADC2_CH4/XTAL_32K_P), J3.7 (DAT0)
SD Card MOSI: ESP1.6 (GPIO6/TOUCH6/ADC1_CH5), J3.3 (CMD)
SDA: ESP1.19 (GPIO11/TOUCH11/ADC2_CH0/FSPID/FSPIIO5/S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), R8.2, U1.24 (SDA/SDI), U2.3 (SDI), U8.18 (SDA/~SPI_CS)
USB +: ESP1.14 (GPIO20/U1CTS/ADC2_CH9/CLK_OUT1/USB_D+), J1.A6 (DP1), J1.B6 (DP2), U7.3, U9.1 (IO1)
USB -: ESP1.13 (GPIO19/U1RTS/ADC2_CH8/CLK_OUT2/USB_D-), J1.A7 (DN1), J1.B7 (DN2), U7.4, U9.4 (IO3)
